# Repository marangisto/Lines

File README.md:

# Lines
Eight-channel line-out conversion module

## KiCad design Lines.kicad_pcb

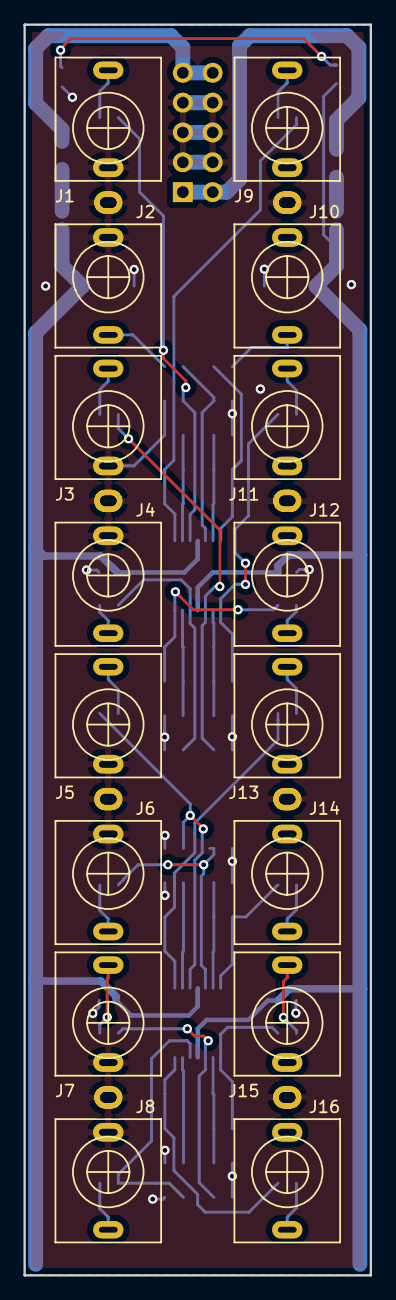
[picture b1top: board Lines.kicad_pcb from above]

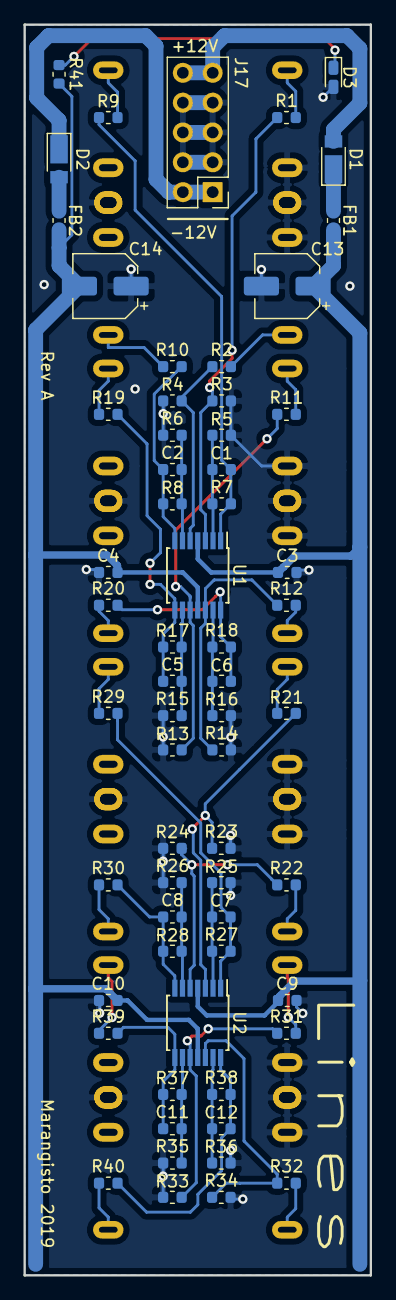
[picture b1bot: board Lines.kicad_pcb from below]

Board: 2 copper layers, 29.5 x 106.5 mm, 79 parts (63 on the bottom side), 48 nets.

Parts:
C1, C2, C5, C6, C7, C8, C11, C12: 220p; C_0603_1608Metric
C3, C4, C9, C10: 100n; C_0603_1608Metric
C13, C14: 22u; CP_Elec_5x5.4
D1, D2: DFLR1400-7; D_PowerDI-123
D3: LED; LED_0603_1608Metric_Castellated
FB1, FB2: Ferrite_Bead; L_0603_1608Metric
J1, J2, J3, J4, J5, J6, J7, J8, J9, J10, J11, J12, J13, J14, J15, J16: AudioJack2_SwitchT; PJ398SM
J17: Conn_02x05_Odd_Even; PinHeader_2x05_P2.54mm_Vertical
R1, R2, R11, R12, R21, R22, R31, R32: 100k; R_0603_1608Metric
R3, R4, R13, R14, R23, R24, R33, R34: 22k; R_0603_1608Metric
R5, R6, R7, R8, R15, R16, R17, R18, R25, R26, R27, R28, R35, R36, R37, R38: 33k; R_0603_1608Metric
R9, R10, R19, R20, R29, R30, R39, R40: 680; R_0603_1608Metric
R41: 1k; R_0603_1608Metric
U1, U2: TL074; TSSOP-14_4.4x5mm_P0.65mm

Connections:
+12V: C3.1, C9.1, C13.1, FB1.1, U1.4, U2.4
-12V: C4.2, C10.2, C14.2, FB2.1, R41.2, U1.11, U2.11
GND: C3.2, C4.1, C9.2, C10.1, C13.2, C14.1, D3.2, J1.S, J1.TN, J2.S, J2.TN, J3.S, J3.TN, J4.S, J4.TN, J5.S, J5.TN, J6.S, J6.TN, J7.S, J7.TN, J8.S, J8.TN, J9.S, J10.S, J11.S, J12.S, J13.S, J14.S, J15.S, J16.S, J17.3, J17.4, J17.5, J17.6, J17.7, J17.8, R3.2, R4.2, R5.1, R6.1, R13.2, R14.2, R15.1, R16.1, R23.2, R24.2, R25.1, R26.1, R33.2, R34.2, R35.1, R36.1
IN1: J1.T, R1.2
IN2: J2.T, R2.2
IN3: J3.T, R11.2
IN4: J4.T, R12.2
IN5: J5.T, R21.2
IN6: J6.T, R22.2
IN7: J7.T, R31.2
IN8: J8.T, R32.2
unnamed: C1.1, R7.2, R9.2, U1.1
unnamed: C1.2, R5.2, R7.1, U1.2
unnamed: C2.1, R8.2, R10.2, U1.7
unnamed: C2.2, R6.2, R8.1, U1.6
unnamed: C5.1, R17.2, R19.2, U1.8
unnamed: C5.2, R15.2, R17.1, U1.9
unnamed: C6.1, R18.2, R20.2, U1.14
unnamed: C6.2, R16.2, R18.1, U1.13
unnamed: C7.1, R27.2, R29.2, U2.1
unnamed: C7.2, R25.2, R27.1, U2.2
unnamed: C8.1, R28.2, R30.2, U2.7
unnamed: C8.2, R26.2, R28.1, U2.6
unnamed: C11.1, R37.2, R39.2, U2.8
unnamed: C11.2, R35.2, R37.1, U2.9
unnamed: C12.1, R38.2, R40.2, U2.14
unnamed: C12.2, R36.2, R38.1, U2.13
unnamed: D1.1, FB1.2
unnamed: D1.2, J17.9, J17.10
unnamed: D2.1, J17.1, J17.2
unnamed: D2.2, FB2.2
unnamed: D3.1, R41.1
unnamed: R1.1, R3.1, U1.3
unnamed: R2.1, R4.1, U1.5
unnamed: R11.1, R13.1, U1.10
unnamed: R12.1, R14.1, U1.12
unnamed: R21.1, R23.1, U2.3
unnamed: R22.1, R24.1, U2.5
unnamed: R31.1, R33.1, U2.10
unnamed: R32.1, R34.1, U2.12
OUT1: J9.T, R9.1
OUT2: J10.T, R10.1
OUT3: J11.T, R19.1
OUT4: J12.T, R20.1
OUT5: J13.T, R29.1
OUT6: J14.T, R30.1
OUT7: J15.T, R39.1
OUT8: J16.T, R40.1

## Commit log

2019-10-27 Initial project skeleton.
2019-10-27 Added drawing and edge cuts.
2019-10-27 Corrected board dimensions and added jacks.
2019-10-27 Complete placement.
2019-10-27 Hand-routed power rails.
2019-10-27 Complete power routing.
2019-10-27 Completed routing.
2019-10-28 Verified on breadboard and corrected input divider value.
2019-10-28 Silk-screens.
2019-10-28 Branding.
2019-10-28 Generated Gerbers.
2019-10-28 Updated PCB with Gerber parameters.
2019-10-31 Added missing files.
2019-10-31 Added BOM.
2019-11-02 Added final panel rendering.
